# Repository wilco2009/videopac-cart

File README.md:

# videopac-cart
Videopac G7000/Magnavox Oddisey ROM Cart

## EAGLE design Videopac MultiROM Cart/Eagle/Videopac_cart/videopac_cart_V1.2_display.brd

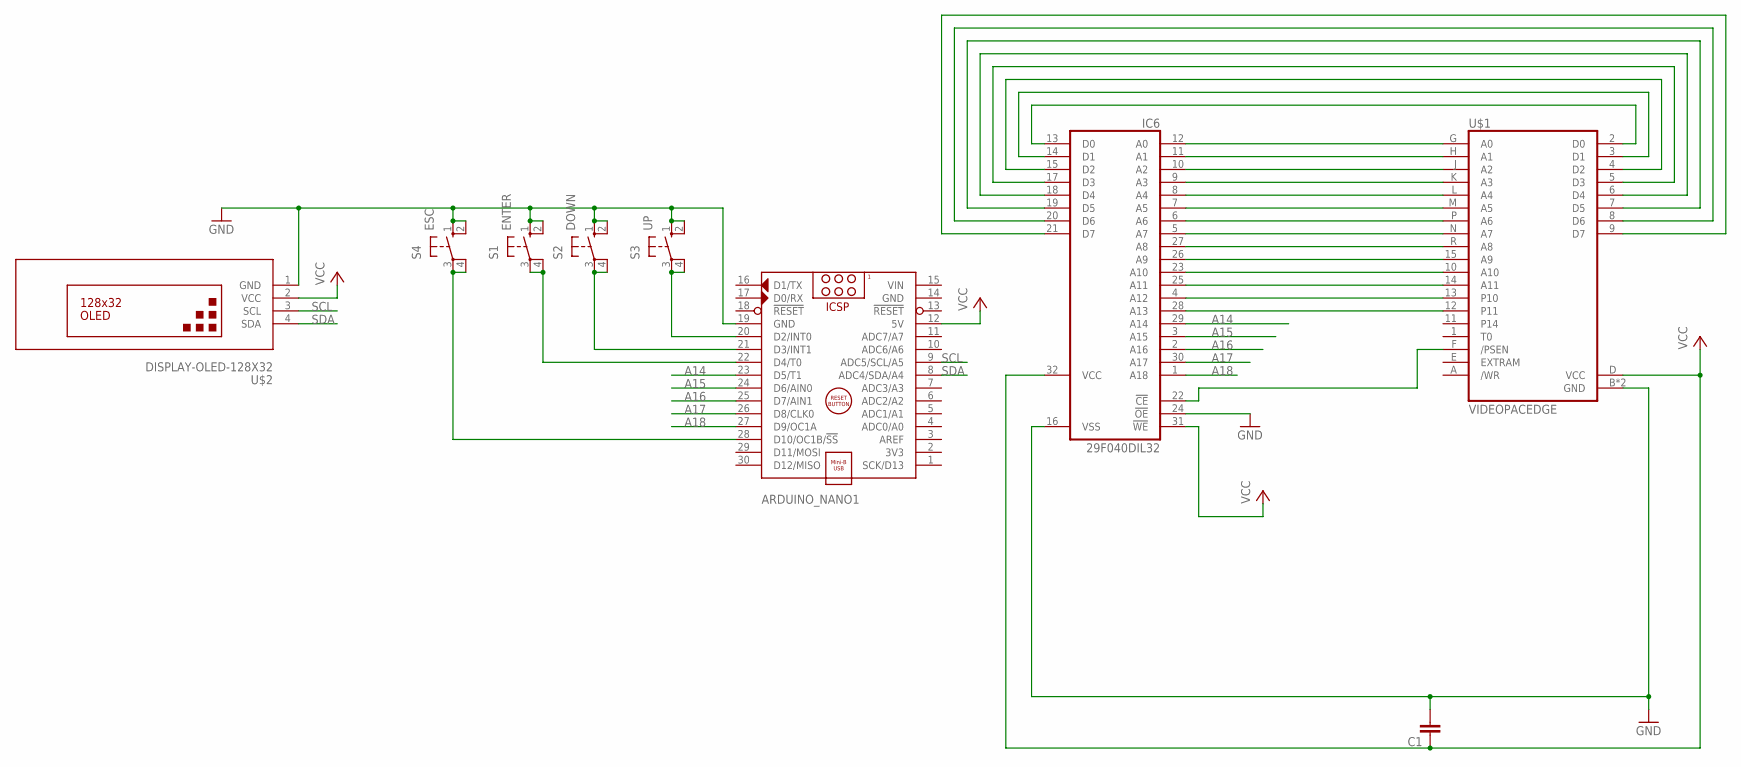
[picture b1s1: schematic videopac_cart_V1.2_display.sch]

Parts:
ARDUINO_NANO1: ARDUINO_NANO
C1: C-EU025-030X050; C025-030X050
IC6: 29F040DIL32; DIL32
S1: ENTER; B3F-10XX
S2: DOWN; B3F-10XX
S3: UP; B3F-10XX
S4: ESC; B3F-10XX
U$1: VIDEOPACEDGE; VIDEOPAC
U$2: DISPLAY-OLED-128X32

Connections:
A14: ARDUINO_NANO1.23 (D5/T1), IC6.29 (A14)
A15: ARDUINO_NANO1.24 (D6/AIN0), IC6.3 (A15)
A16: ARDUINO_NANO1.25 (D7/AIN1), IC6.2 (A16)
A17: ARDUINO_NANO1.26 (D8/CLK0), IC6.30 (A17)
A18: ARDUINO_NANO1.27 (D9/OC1A), IC6.1 (A18)
GND: ARDUINO_NANO1.14 (GND), ARDUINO_NANO1.19 (GND), C1.2, IC6.16 (VSS), IC6.24 (!OE), S1.1 (S), S1.2 (S1), S2.1 (S), S2.2 (S1), S3.1 (S), S3.2 (S1), S4.1 (S), S4.2 (S1), U$1.B (GND), U$1.C (GND), U$2.1 (GND)
unnamed: IC6.12 (A0), U$1.G (A0)
unnamed: IC6.11 (A1), U$1.H (A1)
unnamed: IC6.10 (A2), U$1.J (A2)
unnamed: IC6.9 (A3), U$1.K (A3)
unnamed: IC6.8 (A4), U$1.L (A4)
unnamed: IC6.7 (A5), U$1.M (A5)
unnamed: IC6.6 (A6), U$1.P (A6)
unnamed: IC6.5 (A7), U$1.N (A7)
unnamed: IC6.27 (A8), U$1.R (A8)
unnamed: IC6.26 (A9), U$1.15 (A9)
unnamed: IC6.23 (A10), U$1.10 (A10)
unnamed: IC6.25 (A11), U$1.14 (A11)
unnamed: IC6.4 (A12), U$1.13 (P10)
unnamed: IC6.28 (A13), U$1.12 (P11)
unnamed: ARDUINO_NANO1.28 (D10/OC1B/!SS), S4.3, S4.4 (P1)
unnamed: ARDUINO_NANO1.20 (D2/INT0), S3.3, S3.4 (P1)
unnamed: ARDUINO_NANO1.21 (D3/INT1), S2.3, S2.4 (P1)
unnamed: IC6.22 (!CE), U$1.F (/PSEN)
unnamed: IC6.13 (D0), U$1.2 (D0)
unnamed: IC6.14 (D1), U$1.3 (D1)
unnamed: IC6.15 (D2), U$1.4 (D2)
unnamed: IC6.17 (D3), U$1.5 (D3)
unnamed: IC6.18 (D4), U$1.6 (D4)
unnamed: IC6.19 (D5), U$1.7 (D5)
unnamed: IC6.20 (D6), U$1.8 (D6)
unnamed: IC6.21 (D7), U$1.9 (D7)
unnamed: ARDUINO_NANO1.22 (D4/T0), S1.3, S1.4 (P1)
SCL: ARDUINO_NANO1.9 (ADC5/SCL/A5), U$2.3 (SCL)
SDA: ARDUINO_NANO1.8 (ADC4/SDA/A4), U$2.4 (SDA)
VCC: ARDUINO_NANO1.12 (5V), C1.1, IC6.31 (!WE), IC6.32 (VCC), U$1.D (VCC), U$2.2 (VCC)
VIN: ARDUINO_NANO1.15 (VIN)

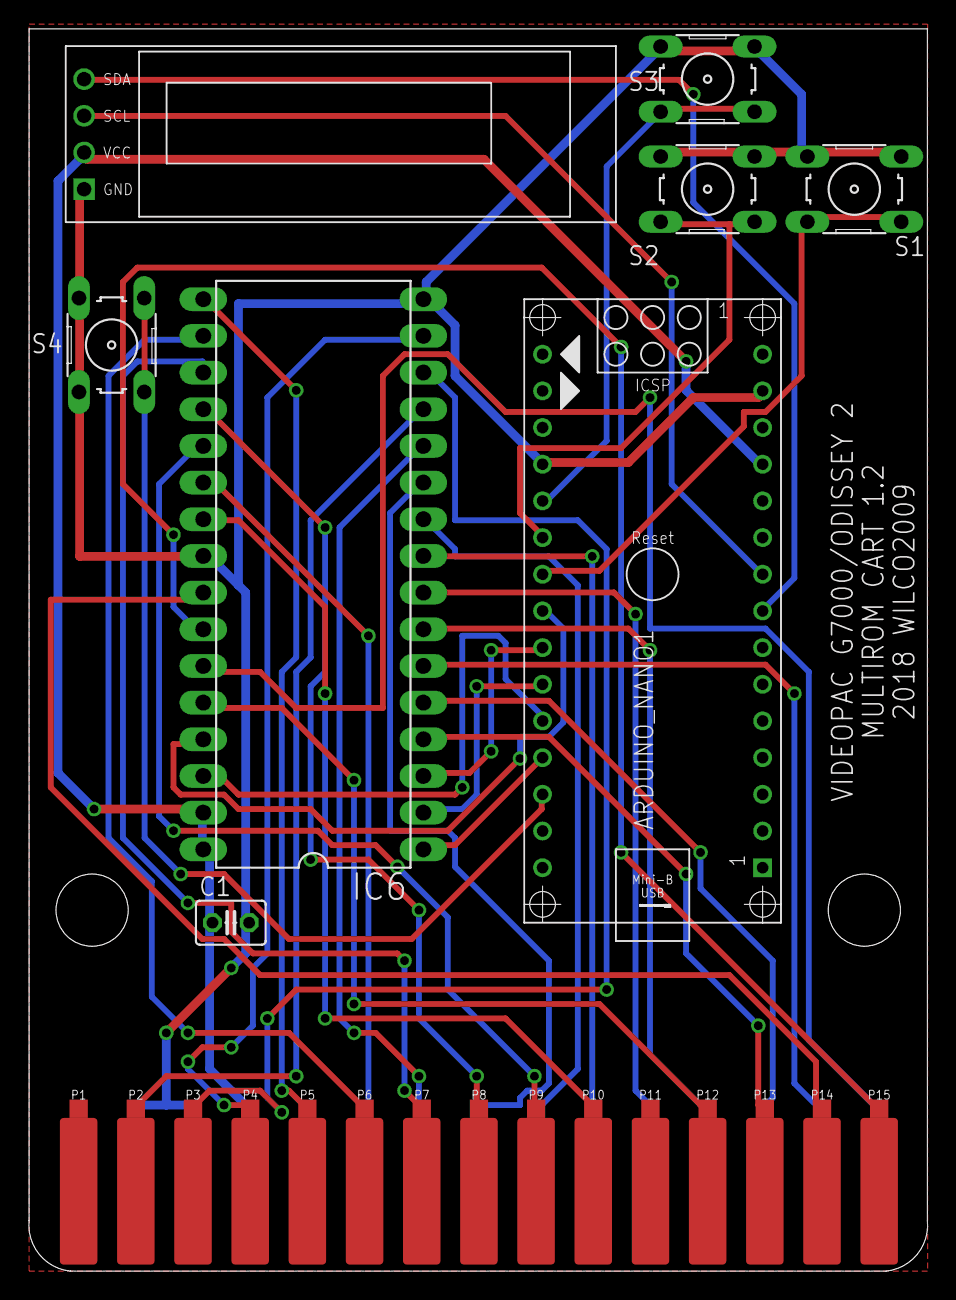
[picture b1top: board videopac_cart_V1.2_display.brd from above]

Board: 2 copper layers, 62.2 x 86.0 mm, 9 parts (0 on the bottom side), 36 nets.

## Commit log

2018-09-10 Version 1.6
    Primera revision en Github del Videopac ROM Maker
2018-09-10 Eagle and arduino software added
2018-09-10 ROMSet Maker updated to 1.61
2018-09-30 Arduino program updated to 1.1
    Arduino program updated to 1.1 Descriptions modified

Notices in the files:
parts and their libraries:
diy-modules: Released under the Creative Commons Attribution 4.0 International License: http://creativecommons.org/licenses/by/4.0
